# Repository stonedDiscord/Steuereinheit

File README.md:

# Schaltplan Steuereinheit 68000

Zweck ist es die genauen Pinouts aller Stecker für Diagnosezwecken und die Verläufe der Leiterbahnen für Reparaturzwecke zu dokumentieren.

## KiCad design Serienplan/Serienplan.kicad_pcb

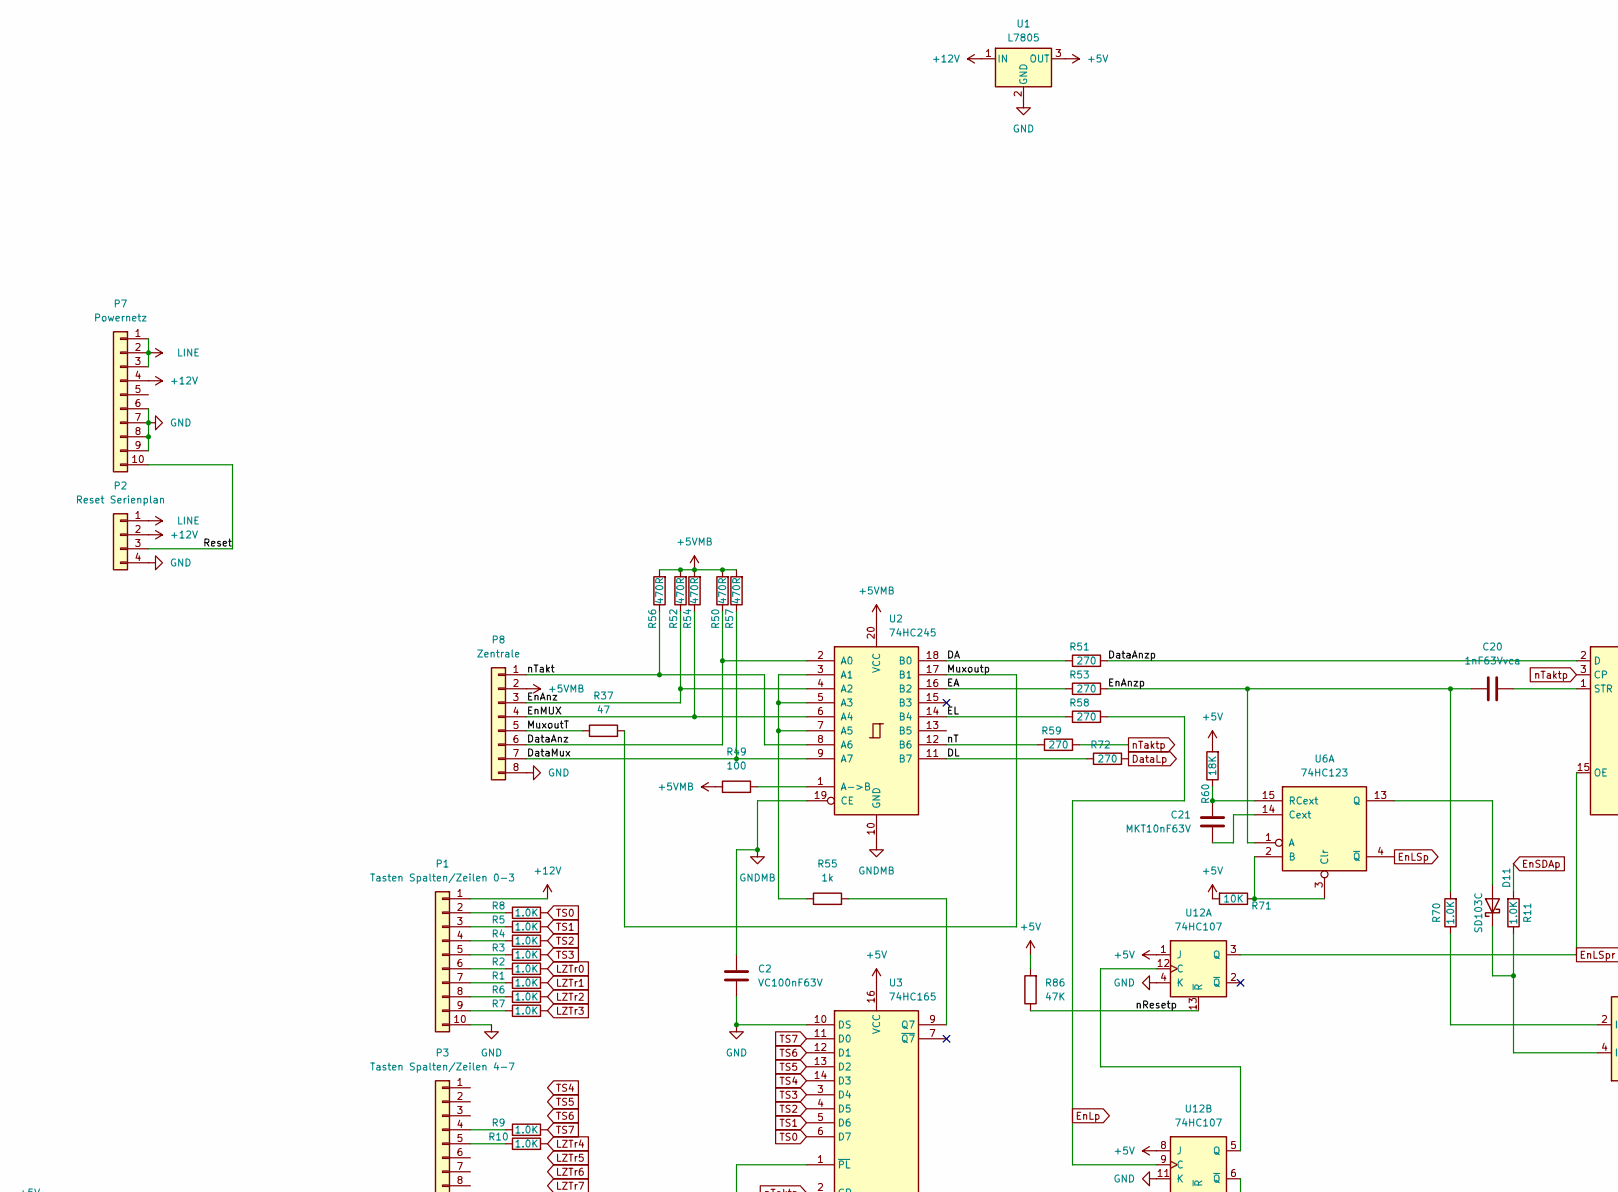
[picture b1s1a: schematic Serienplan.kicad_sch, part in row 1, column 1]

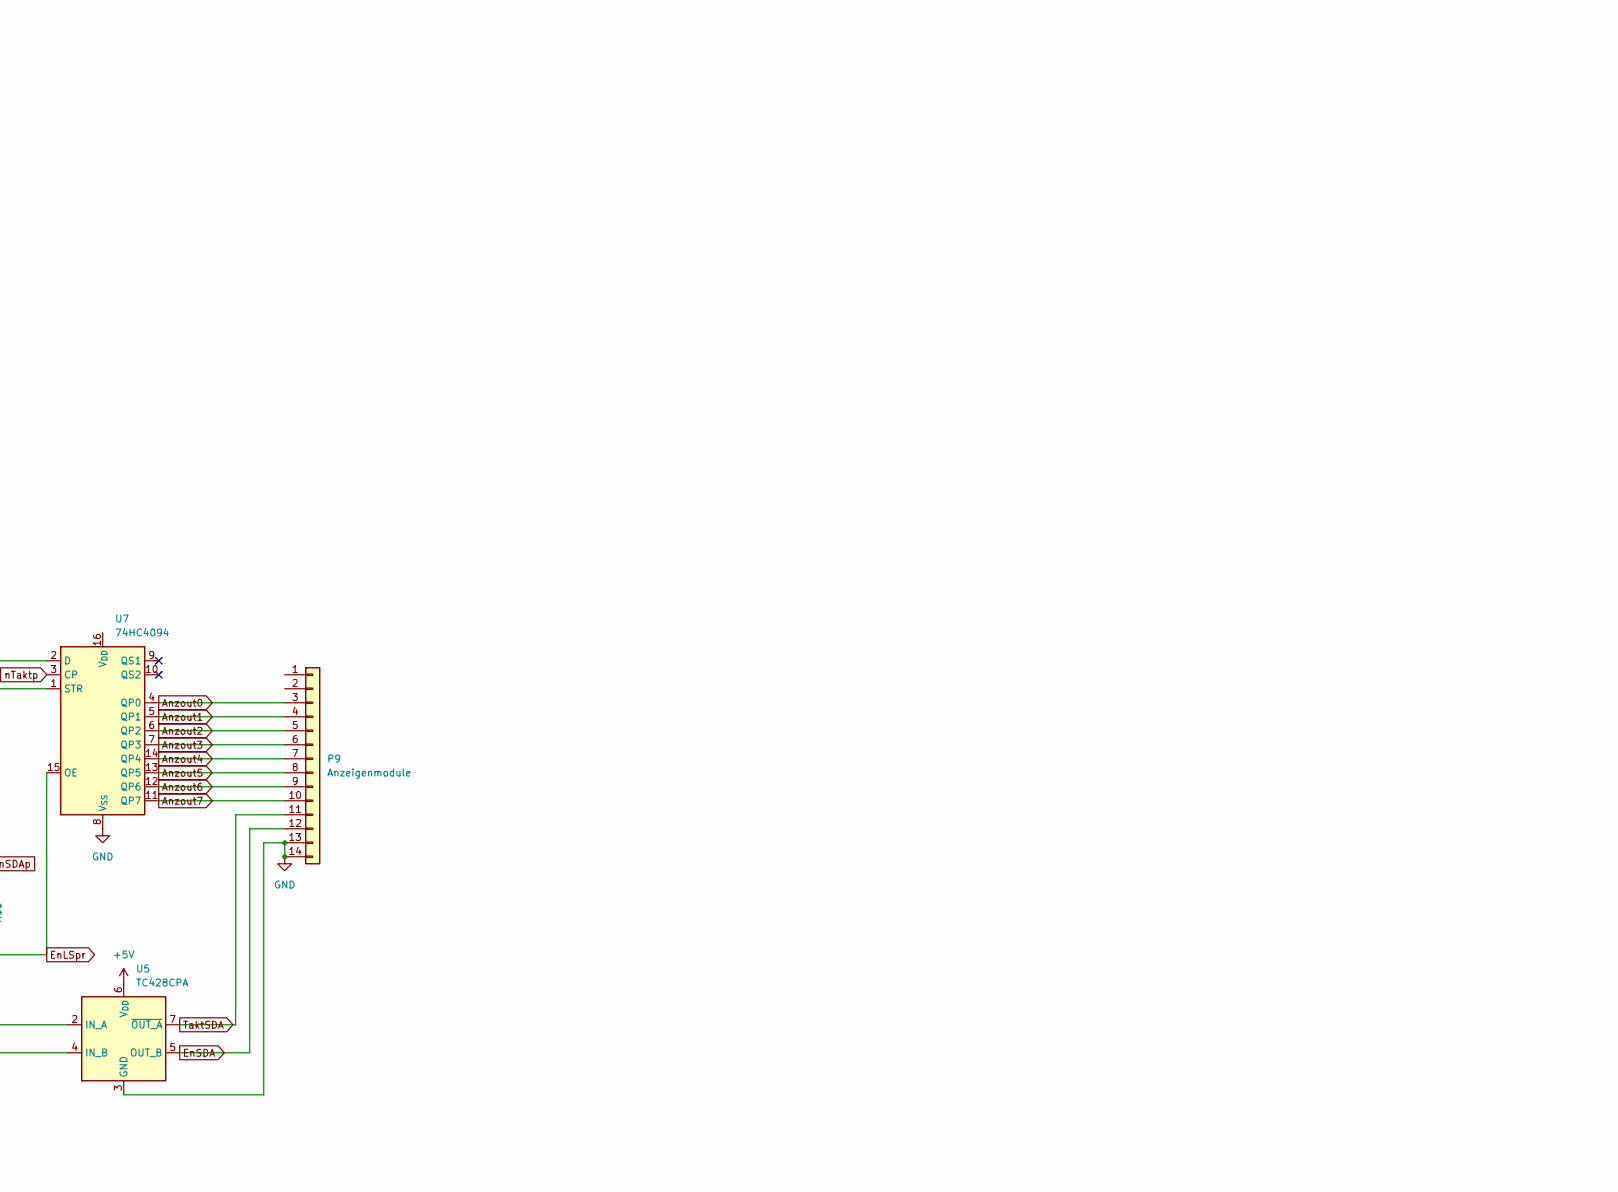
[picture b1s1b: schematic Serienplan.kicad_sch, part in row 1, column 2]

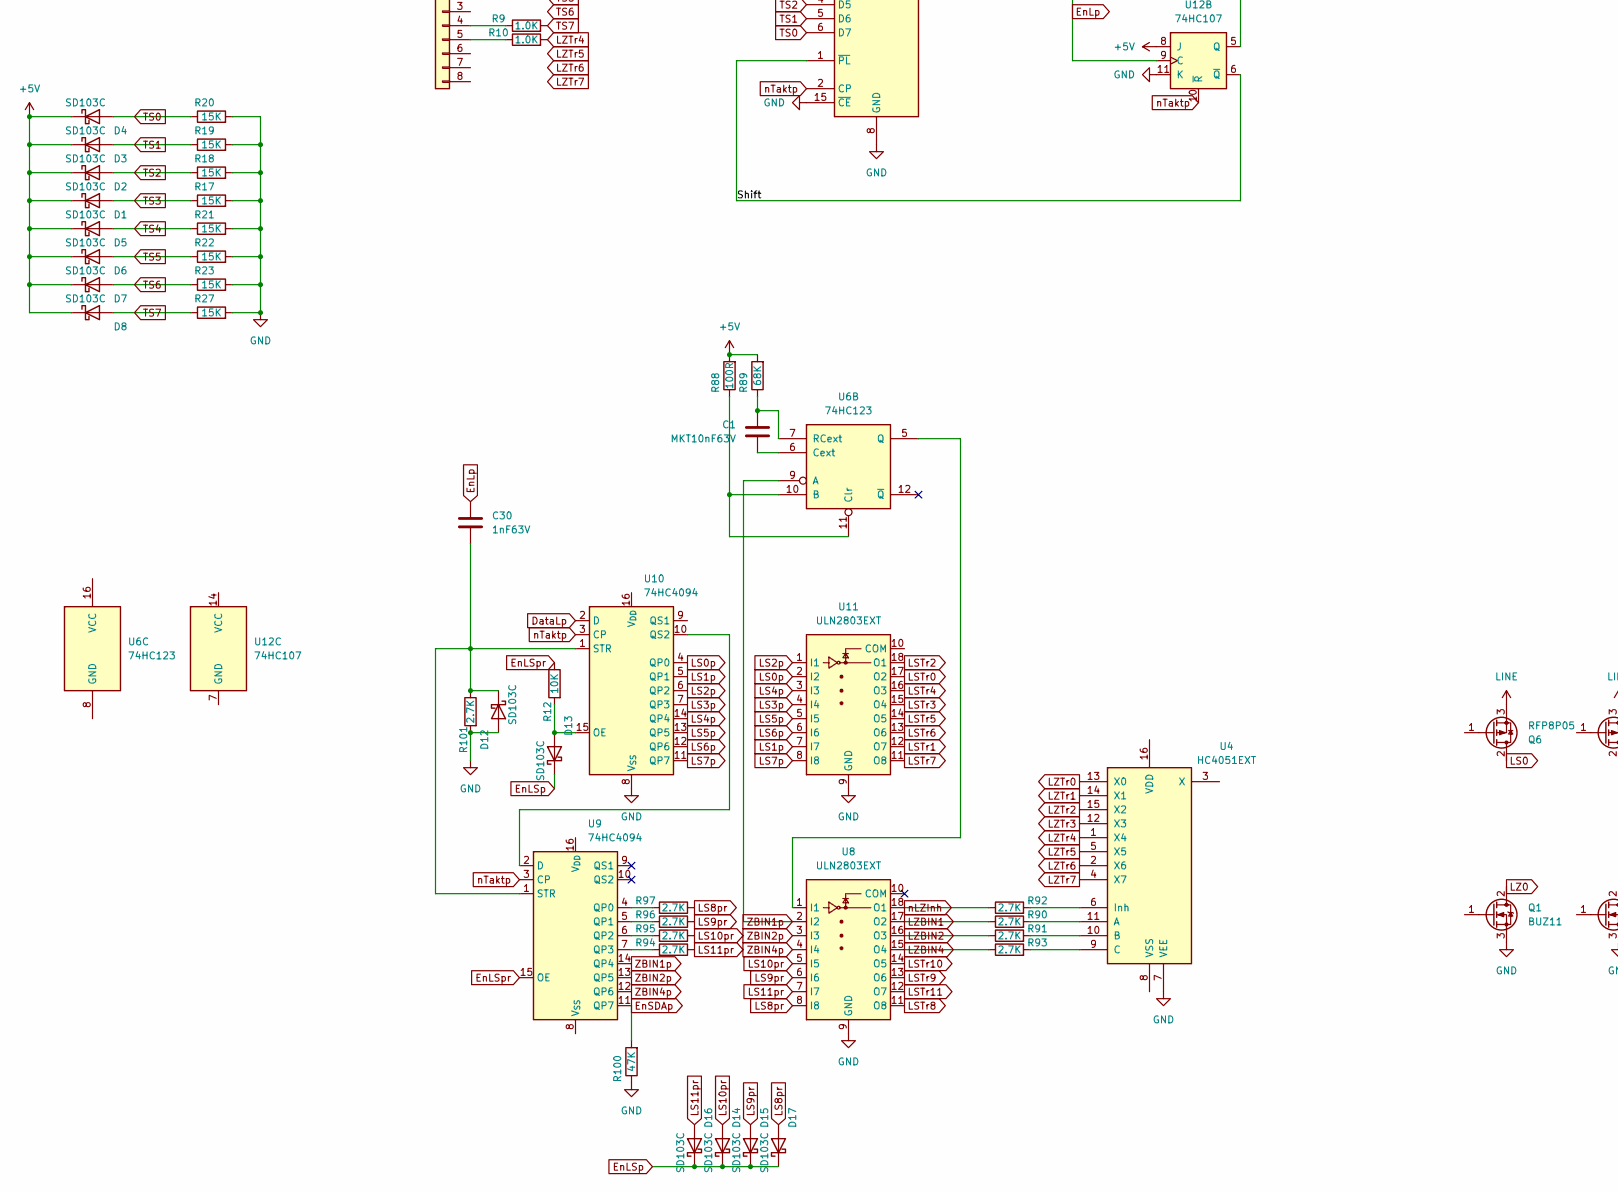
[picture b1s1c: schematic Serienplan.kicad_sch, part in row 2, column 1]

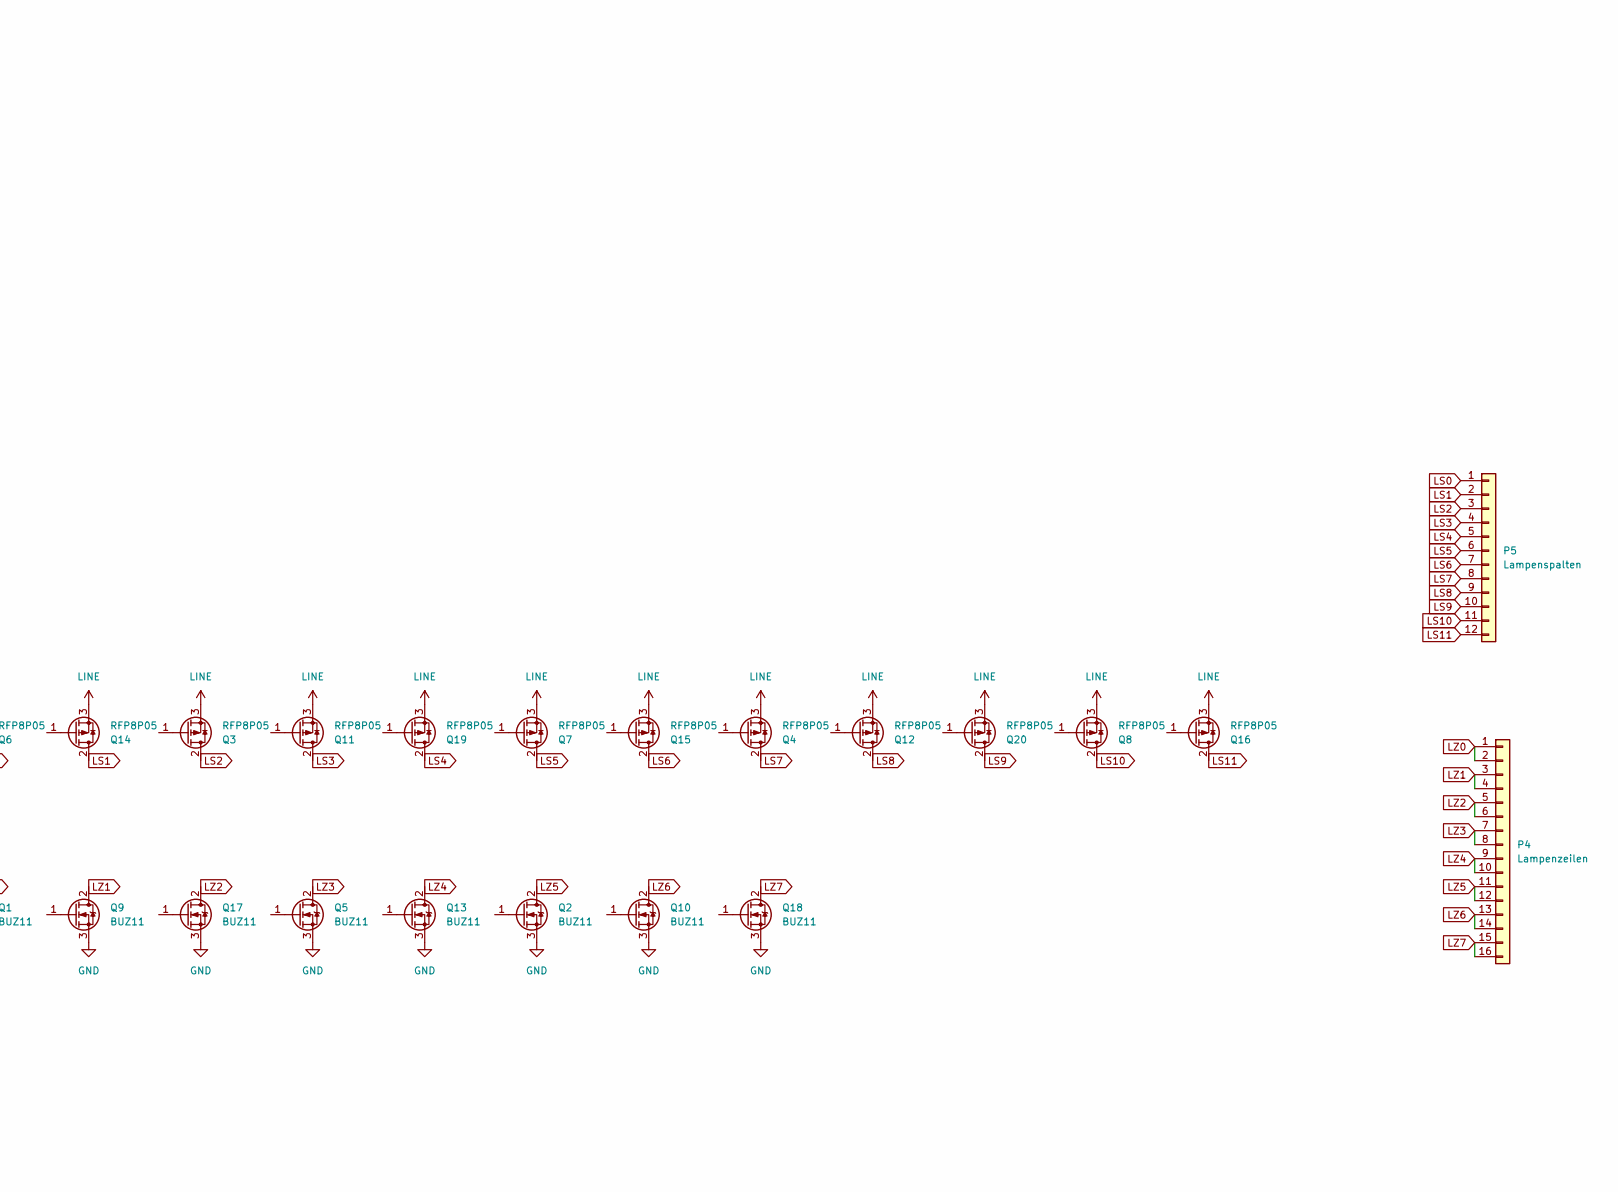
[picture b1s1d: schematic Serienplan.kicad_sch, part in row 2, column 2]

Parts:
C1, C21: MKT10nF63V
C2: VC100nF63V
C20: 1nF63Vvca
C30: 1nF63V
D1, D2, D3, D4, D5, D6, D7, D8, D11, D12, D13, D14, D15, D16, D17: SD103C; D_DO-35_SOD27_P7.62mm_Horizontal
P1: Tasten Spalten/Zeilen 0-3; Stocko_MKS_1660-6-0-1010_1x10_P2.50mm_Vertical
P2: Reset Serienplan; Stocko_MKS_1654-6-0-404_1x4_P2.50mm_Vertical
P3: Tasten Spalten/Zeilen 4-7; Stocko_MKS_1658-6-0-808_1x8_P2.50mm_Vertical
P4: Lampenzeilen; Stocko_MKS_1666-6-0-1616_1x16_P2.50mm_Vertical
P5: Lampenspalten; Stocko_MKS_1662-6-0-1212_1x12_P2.50mm_Vertical
P7: Powernetz; Stocko_MKS_1660-6-0-1010_1x10_P2.50mm_Vertical
P8: Zentrale; Stocko_MKS_1658-6-0-808_1x8_P2.50mm_Vertical
P9: Anzeigenmodule; Stocko_MKS_1664-6-0-1414_1x14_P2.50mm_Vertical
Q1, Q2, Q5, Q9, Q10, Q13, Q17, Q18: BUZ11; TO-220-3_Horizontal_TabUp
Q3, Q4, Q6, Q7, Q8, Q11, Q12, Q14, Q15, Q16, Q19, Q20: RFP8P05; TO-220-3_Horizontal_TabUp
R1, R2, R3, R4, R5, R6, R7, R8, R9, R10, R11, R70: 1.0K; R_Axial_DIN0204_L3.6mm_D1.6mm_P7.62mm_Horizontal
R12, R71: 10K; R_Axial_DIN0204_L3.6mm_D1.6mm_P7.62mm_Horizontal
R17, R18, R19, R20, R21, R22, R23, R27: 15K; R_Axial_DIN0204_L3.6mm_D1.6mm_P7.62mm_Horizontal
R37: 47; R_Axial_DIN0204_L3.6mm_D1.6mm_P7.62mm_Horizontal
R49: 100; R_Axial_DIN0204_L3.6mm_D1.6mm_P7.62mm_Horizontal
R50, R52, R54, R56, R57: 470R; R_Axial_DIN0204_L3.6mm_D1.6mm_P7.62mm_Horizontal
R51, R53, R58, R59, R72: 270; R_Axial_DIN0204_L3.6mm_D1.6mm_P7.62mm_Horizontal
R55: 1k; R_Axial_DIN0204_L3.6mm_D1.6mm_P7.62mm_Horizontal
R60: 18K; R_Axial_DIN0204_L3.6mm_D1.6mm_P7.62mm_Horizontal
R86, R100: 47K; R_Axial_DIN0204_L3.6mm_D1.6mm_P7.62mm_Horizontal
R88: 100R; R_Axial_DIN0204_L3.6mm_D1.6mm_P7.62mm_Horizontal
R89: 68K; R_Axial_DIN0204_L3.6mm_D1.6mm_P7.62mm_Horizontal
R90, R91, R92, R93, R94, R95, R96, R97, R101: 2.7K; R_Axial_DIN0204_L3.6mm_D1.6mm_P7.62mm_Horizontal
U1: L7805; TO-220F-3_Horizontal_TabDown
U2: 74HC245; DIP-20_W7.62mm
U3: 74HC165; DIP-16_W7.62mm
U4: HC4051EXT; DIP-16_W7.62mm
U5: TC428CPA; DIP-8_W7.62mm
U6: 74HC123; DIP-16_W7.62mm
U7, U9, U10: 74HC4094; DIP-16_W7.62mm
U8, U11: ULN2803EXT; DIP-18_W7.62mm
U12: 74HC107; DIP-14_W7.62mm

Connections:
+5V: D1.1 (K), D2.1 (K), D3.1 (K), D4.1 (K), D5.1 (K), D6.1 (K), D7.1 (K), D8.1 (K), R60.2, R71.2, R86.2, R88.2, R89.2, U1.3 (OUT), U3.16 (VCC), U5.6 (V_{DD}), U12.1 (J), U12.8 (J)
+5VMB: P8.2, R49.1, R50.2, R52.2, R54.2, R56.2, R57.2, U2.20 (VCC)
+12V: P1.1, P2.2, P7.4, U1.1 (IN)
/DA: R51.1, U2.18 (B0)
/DL: R72.1, U2.11 (B7)
/DataAnz: P8.6, R50.1, U2.2 (A0)
/DataAnzp: R51.2, U7.2 (D)
/DataMux: P8.7, R57.1, U2.9 (A7)
/EA: R53.1, U2.16 (B2)
/EL: R58.1, U2.14 (B4)
/EnAnz: P8.3, R52.1, U2.4 (A2)
/EnAnzp: C20.1, R53.2, R70.2, U6.1 (A)
/EnMUX: P8.4, R54.1, U2.6 (A4)
/MuxoutT: P8.5, R37.1
/Muxoutp: R37.2, U2.17 (B1)
/Reset: P2.3, P7.10
/Shift: U3.1 (~PL), U12.6 (~Q)
/nResetp: R86.1, U12.13 (~R)
/nT: R59.1, U2.12 (B6)
/nTakt: P8.1, R56.1, U2.8 (A6)
Anzout0: P9.3, U7.4 (QP0)
Anzout1: P9.4, U7.5 (QP1)
Anzout2: P9.5, U7.6 (QP2)
Anzout3: P9.6, U7.7 (QP3)
Anzout4: P9.7, U7.14 (QP4)
Anzout5: P9.8, U7.13 (QP5)
Anzout6: P9.9, U7.12 (QP6)
Anzout7: P9.10, U7.11 (QP7)
DataLp: R72.2, U10.2 (D)
EnLSp: D13.1 (K), D14.1 (K), D15.1 (K), D16.1 (K), D17.1 (K), U6.4 (~Q)
EnLSpr: R12.1, U7.15 (OE), U9.15 (OE), U12.3 (Q)
EnLp: C30.1, R58.2, U12.9 (C)
EnSDA: P9.12, U5.5 (OUT_B)
EnSDAp: R11.2, R100.2, U9.11 (QP7)
GND: C2.2, D12.2 (A), P1.10, P2.4, P7.6, P7.7, P7.8, P7.9, P8.8, P9.13, P9.14, Q1.3 (S), Q2.3 (S), Q5.3 (S), Q9.3 (S), Q10.3 (S), Q13.3 (S), Q17.3 (S), Q18.3 (S), R17.2, R18.2, R19.2, R20.2, R21.2, R22.2, R23.2, R27.2, R100.1, R101.2, U1.2 (GND), U3.8 (GND), U3.10 (DS), U3.15 (~CE), U4.7 (VEE), U5.3 (GND), U7.8 (V_{SS}), U8.9 (GND), U10.8 (V_{SS}), U11.9 (GND), U12.4 (K), U12.11 (K)
GNDMB: C2.1, U2.10 (GND), U2.19 (CE)
LINE: P2.1, P7.1, P7.2, P7.3, Q3.3 (S), Q4.3 (S), Q6.3 (S), Q7.3 (S), Q8.3 (S), Q11.3 (S), Q12.3 (S), Q14.3 (S), Q15.3 (S), Q16.3 (S), Q19.3 (S), Q20.3 (S)
LS0: P5.1, Q6.2 (D)
LS0p: U10.4 (QP0), U11.2 (I2)
LS1: P5.2, Q14.2 (D)
LS1p: U10.5 (QP1), U11.7 (I7)
LS2: P5.3, Q3.2 (D)
LS2p: U10.6 (QP2), U11.1 (I1)
LS3: P5.4, Q11.2 (D)
LS3p: U10.7 (QP3), U11.4 (I4)
LS4: P5.5, Q19.2 (D)
LS4p: U10.14 (QP4), U11.3 (I3)
LS5: P5.6, Q7.2 (D)
LS5p: U10.13 (QP5), U11.5 (I5)
LS6: P5.7, Q15.2 (D)
LS6p: U10.12 (QP6), U11.6 (I6)
LS7: P5.8, Q4.2 (D)
LS7p: U10.11 (QP7), U11.8 (I8)
LS8: P5.9, Q12.2 (D)
LS8pr: D17.2 (A), R97.1, U8.8 (I8)
LS9: P5.10, Q20.2 (D)
LS9pr: D15.2 (A), R96.1, U8.6 (I6)
LS10: P5.11, Q8.2 (D)
LS10pr: D14.2 (A), R95.1, U8.5 (I5)
LS11: P5.12, Q16.2 (D)
LS11pr: D16.2 (A), R94.1, U8.7 (I7)
LSTr0: U11.17 (O2)
LSTr1: U11.12 (O7)
LSTr2: U11.18 (O1)
LSTr3: U11.15 (O4)
LSTr4: U11.16 (O3)
LSTr5: U11.14 (O5)
LSTr6: U11.13 (O6)
LSTr7: U11.11 (O8)
LSTr8: U8.11 (O8)
LSTr9: U8.13 (O6)
LSTr10: U8.14 (O5)
LSTr11: U8.12 (O7)
LZ0: P4.1, P4.2, Q1.2 (D)
LZ1: P4.3, P4.4, Q9.2 (D)
LZ2: P4.5, P4.6, Q17.2 (D)
LZ3: P4.7, P4.8, Q5.2 (D)
LZ4: P4.9, P4.10, Q13.2 (D)
LZ5: P4.11, P4.12, Q2.2 (D)
LZ6: P4.13, P4.14, Q10.2 (D)
LZ7: P4.15, P4.16, Q18.2 (D)
LZBIN1: R90.1, U8.17 (O2)
LZBIN2: R91.1, U8.16 (O3)
LZBIN4: R93.1, U8.15 (O4)
LZTr0: R2.2, U4.13 (X0)
LZTr1: R1.2, U4.14 (X1)
LZTr2: R6.2, U4.15 (X2)
LZTr3: R7.2, U4.12 (X3)
LZTr4: R10.2, U4.1 (X4)
LZTr5: U4.5 (X5)
LZTr6: U4.2 (X6)
LZTr7: U4.4 (X7)
unnamed: D11.2 (A), U6.13 (Q)
unnamed: D11.1 (K), R11.1, U5.4 (IN_B)
unnamed: C30.2, D12.1 (K), R101.1, U9.1 (STR), U10.1 (STR)
unnamed: D13.2 (A), R12.2, U10.15 (OE)
unnamed: P1.2, R8.1
unnamed: P1.3, R5.1
unnamed: P1.4, R4.1
unnamed: P1.5, R3.1
unnamed: P1.6, R2.1
unnamed: P1.7, R1.1
unnamed: P1.8, R6.1
unnamed: P1.9, R7.1
unnamed: P3.4, R9.1
unnamed: P3.5, R10.1
unnamed: R55.1, U2.3 (A1), U2.5 (A3), U2.7 (A5)
unnamed: R49.2, U2.1 (A->B)
unnamed: R55.2, U3.9 (Q7)
unnamed: R90.2, U4.11 (A)
unnamed: R91.2, U4.10 (B)
unnamed: R93.2, U4.9 (C)
unnamed: R92.2, U4.6 (Inh)
unnamed: R70.1, U5.2 (IN_A)
unnamed: R71.1, U6.2 (B), U6.3 (Clr)
unnamed: C21.2, U6.14 (Cext)
unnamed: C21.1, R60.1, U6.15 (RCext)
unnamed: R88.1, U6.10 (B), U6.11 (Clr)
unnamed: C1.2, U6.6 (Cext)
unnamed: U6.5 (Q), U8.1 (I1)
unnamed: C1.1, R89.1, U6.7 (RCext)
unnamed: C20.2, U7.1 (STR)
unnamed: R97.2, U9.4 (QP0)
unnamed: R96.2, U9.5 (QP1)
unnamed: R95.2, U9.6 (QP2)
unnamed: R94.2, U9.7 (QP3)
unnamed: U9.2 (D), U10.10 (QS2)
unnamed: U12.5 (Q), U12.12 (C)
TS0: D4.2 (A), R8.2, R20.1, U3.6 (D7)
TS1: D3.2 (A), R5.2, R19.1, U3.5 (D6)
TS2: D2.2 (A), R4.2, R18.1, U3.4 (D5)
TS3: D1.2 (A), R3.2, R17.1, U3.3 (D4)
TS4: D5.2 (A), R21.1, U3.14 (D3)
TS5: D6.2 (A), R22.1, U3.13 (D2)
TS6: D7.2 (A), R23.1, U3.12 (D1)
TS7: D8.2 (A), R9.2, R27.1, U3.11 (D0)
TaktSDA: P9.11, U5.7 (~OUT_A)
ZBIN1p: U6.9 (A), U8.2 (I2), U9.14 (QP4)
ZBIN2p: U8.3 (I3), U9.13 (QP5)
ZBIN4p: U8.4 (I4), U9.12 (QP6)
nLZInh: R92.1, U8.18 (O1)
nTaktp: R59.2, U3.2 (CP), U7.3 (CP), U9.3 (CP), U10.3 (CP), U12.10 (~R)

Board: 2 copper layers, 104 parts (0 on the bottom side), 124 nets, no tracks yet.
